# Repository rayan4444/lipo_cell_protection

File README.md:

# [project name]

Here goes a short project description

## Features
A list of the baords's features and functions, what it needs as input to function, etc. 

A bloc diagram is always useful to have here

## Pinouts

Here you can drop connectors and microcontroller pinouts. Anything that could be
useful when conencting or programming the board

|Signal|Pin|Notes|
|:---:|:----:|:---:|
|Button|P0.12|active low|

> note: [WireViz](https://github.com/wireviz/WireViz) is a good tool to document
connectors and wire harnesses

## Errata / Wishlist 
Known issues, limitations, errors and their workarounds. This is also a good place
to drop notes on what should be done in the next revision. 

## Additional notes on how to use this template
* Create your kicad project, shcematics and pcb files in this repository
* Gerber files and BOM go into the Production folder 
* Images, text and design notes go into the Documentation folder 
* Datasheets and application notes go into the Datasheets folder
* Make a new release tag for every manufactured revision of the board, work on a
separate branch for new revisions
* Optinally: you can keep track of testing notes and results in a new Testing folder

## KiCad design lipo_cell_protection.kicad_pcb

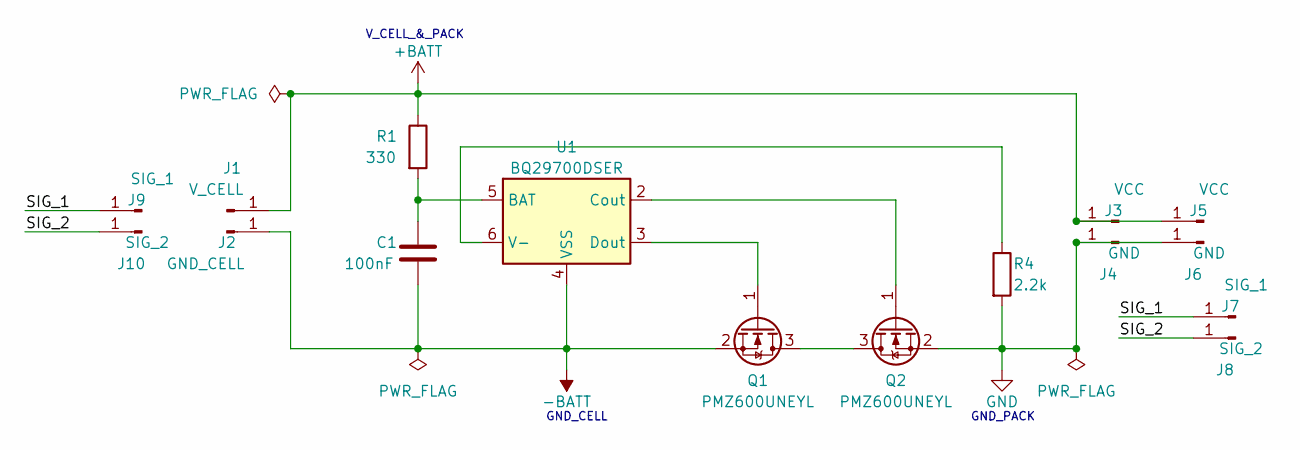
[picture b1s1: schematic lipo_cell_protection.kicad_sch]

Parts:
C1: 100nF; C_0201_0603Metric
J1: V_CELL; TestPoint_Pad_D1.0mm
J2: GND_CELL; TestPoint_Pad_D1.0mm
J3, J5: VCC; TestPoint_Pad_D1.0mm
J4, J6: GND; TestPoint_Pad_D1.0mm
J7, J9: SIG_1; TestPoint_Pad_D1.0mm
J8, J10: SIG_2; TestPoint_Pad_D1.0mm
Q1, Q2: PMZ600UNEYL; SOT-883
R1: 330; R_0201_0603Metric; Tolerance 1%
R4: 2.2k; R_0201_0603Metric
U1: BQ29700DSER; WSON-6_1.5x1.5mm_P0.5mm

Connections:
+BATT: J1.1, J3.1, J5.1, R1.1
-BATT: C1.2, J2.1, Q1.2 (S), U1.4 (VSS)
/SIG_1: J7.1, J9.1
/SIG_2: J8.1, J10.1
GND: J4.1, J6.1, Q2.2 (S), R4.2
unnamed: Q1.3 (D), Q2.3 (D)
unnamed: Q1.1 (G), U1.3 (Dout)
unnamed: Q2.1 (G), U1.2 (Cout)
unnamed: C1.1, R1.2, U1.5 (BAT)
unnamed: R4.1, U1.6 (V-)

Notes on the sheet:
GND_CELL
V_CELL_&_PACK
GND_PACK

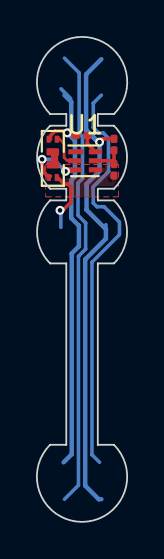
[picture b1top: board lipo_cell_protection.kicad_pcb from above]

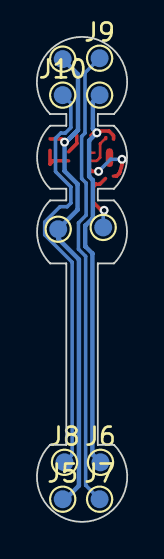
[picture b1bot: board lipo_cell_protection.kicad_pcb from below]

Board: 2 copper layers, 5.0 x 26.9 mm, 16 parts (10 on the bottom side), 10 nets.

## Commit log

2023-10-18 first pass
2023-10-18 round attempt
2023-10-28 full
